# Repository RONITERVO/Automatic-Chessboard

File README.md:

# Automatic Chessboard

Arduino firmware for a CoreXY automatic chessboard with:

- two STEP/DIR stepper-motor drivers;
- an electromagnet for moving pieces;
- a multiplexed 8x8 reed-sensor matrix;
- a 16x2 I2C LCD and two-button interface; and
- the Micro-Max chess engine.

This is a substantially modified implementation of Greg06's
[Automated Chessboard](https://www.instructables.com/Automated-Chessboard/),
adapted around salvaged 3D-printer mechanics and the tested electronics
documented in this repository. See [design lineage and
attribution](ATTRIBUTION.md) and the repository's
[multi-license map](LICENSE.md) before redistributing it.

The [immersive 3D simulator](https://ronitervo.github.io/Automatic-Chessboard/) presents the complete assembly, chess pieces, setup process, physical controls, LCD, Arduino signal flow, wiring, and full-history replay in one shared React Three Fiber world. Visitors can use mouse, touch, or supported WebXR hands/controllers at real-world scale while the compiled production Nano HEX drives power-on, calibration, reed sensing, Micro-Max decisions, STEP/DIR motion, and magnet control. The standalone experience exposes Bluetooth as disconnected and never requests a real device. It is published automatically from `site/` after changes reach `main`.

## Demo

https://github.com/user-attachments/assets/5234de29-f910-4aed-a476-050bdca1a51d

## Hardware assumptions

The sketch uses the pin assignments and motion calibration in `global.h`. The
motor interface expects STEP/DIR drivers such as the A4988; motor current and
microstep selection are configured on the driver hardware.

For a complete beginner-oriented build, start with the
[`hardware` build guide](hardware/README.md). It includes protected power
wiring, a BOM, exact Nano/MKS Gen L V1.0 and 64-square sensor maps, staged assembly,
commissioning checks, diagrams, photographs of the working prototype, and
rework notes for the operational long PCB whose design predates the current
Bluetooth and A6 additions. Its archived KiCad source is reference-only, not a
current fabrication release. The 5 V buck output belongs on the Nano `5V` pin,
not `VIN`.

## Building

The release build is reproducible from PowerShell:

```powershell
./firmware/test.ps1 -InstallDependencies
```

It pins the AVR core and display libraries, validates the hardware contract,
runs tool tests, compiles the classic Nano and MKS Gen L V1.0 profiles, and
enforces flash/SRAM budgets. See [`firmware/README.md`](firmware/README.md) for the
modular source layout, explicit upload command, and contributor policy. The
main `.ino` can still be opened normally in Arduino IDE; its sibling `.ino`
tabs are compiled together automatically.

Review the pin assignments, travel calibration, limit-switch behavior, driver
current limit, and microstep settings before powering the motion hardware.

## Full validation without motion

When motors, piece magnets, or trustworthy reed readings are unavailable, run:

```powershell
./test-no-motion.ps1 -Port COM7
```

The workflow compiles the Nano firmware, enforces its memory budgets, exhaustively
tests the motionless `PLAN` / `DRAG` / `COMMIT` occupancy model, runs Windows and
Android planner/protocol/simulator tests, builds both apps, and optionally samples
the real Nano over USB. The COM probe is allowlisted to `HELLO 5.1.0`, `INFO`,
`TELEM`, and `BOARD`; it validates BOARD framing but does not require any particular
occupancy. It never uploads firmware or requests calibration, motor steps, magnet
power, or a chess move.

The probe first tries to keep DTR/RTS inactive. If a classic Nano does not
answer without its normal USB reset, use `-AllowSerialReset` only after checking
that firmware startup cannot energize the mechanism; this still does not send
an upload or any motion-capable protocol command.

This is the strongest release test possible without actuation, but it cannot prove
motor direction or step accuracy, magnet current/pickup/release, reed wiring and
orientation, mechanical clearance, homing repeatability, or physical collision
behavior. Those remain staged commissioning checks.

## Windows and Bluetooth companion

`windows_app` is the public-ready, open-source Windows monitor and companion for
this firmware. Windows runs Stockfish 18 and full chess rules while the Nano
retains motor timing, sensor scanning, calibration, limit checks, and Micro-Max
as a standalone fallback. It supports the Nano USB port, HC-08 BLE using the
default `FFE0`/`FFE1` service, and a no-hardware simulator for contributors.

Run `windows_app/setup.ps1` once, then `windows_app/run.ps1`. The visual Monitor
shows physical occupancy mismatches, carriage state, magnet command, limit
inputs, firmware memory, uptime, and connection freshness. Guided diagnostics,
structured logs, privacy-sanitized support bundles, optional local camera view,
automatic reconnect, and guarded developer controls are included. Start with
**Diagnostics -> Run safe diagnostics**; it never moves hardware. **Start game
and calibrate** intentionally begins physical movement.

The HC-08 receives commands on D10 through a receive-only software UART and
gets replies from hardware TX/D1. D0 remains dedicated to the onboard USB
bridge, so Bluetooth and USB transmitters never fight electrically. To free
D10, Button B/black limit uses analog-only A6 with a required external 10 kOhm
pull-up to 5 V. The HC-08 RX input must receive 3.3 V logic through a divider.
See `windows_app/README.md` for the complete wiring and first-start procedure.

Firmware 5.1.0 makes software occupancy authoritative. The reed matrix is read
only when a human requests move detection with Button A. The LCD proposes the
move; a second A press accepts it, while B opens square correction. Starting
pieces and robot moves are never checked against the reeds. A false reading
cannot stop a game. Both apps use the same workflow and exact `HELLO 5.1.0`
release handshake. See [Human-confirmed play](firmware/HUMAN_MOVE_INPUT.md) for
controls, correction, captures, and companion behavior.

Host-planned rearrangements still use straight orthogonal drags, explicit
capture removal, and independently tracked software occupancy. En passant,
promotion, and standard castling are included. Motor faults, calibration,
magnet timeout, `STOP`, and the single-byte `!` halt retain their behavior.

For local Micro-Max play, firmware 5.1.0 automatically carries knights and
blocked direct moves through the shortest available sequence of empty,
orthogonally adjacent square centres. It retains manual placement only when no
empty route connects the move endpoints. If a capture itself cannot reach the
bin, the player may remove it when prompted; after confirmation, the Nano
reruns the route search and completes the AI move automatically when possible.

Boards with missing, intermittent, or deliberately unused reed switches can use
the explicit **Move by tapping app** mode in either companion. Both human and
Stockfish moves then originate in the app and use the same physical route
planner. The app and Nano maintain matching virtual occupancy and ignore reed
readings for that entire game. The user visually confirms every completed move;
any mismatch or lost connection stops play and requires inspection and a new
calibrated session. This is an explicit authority choice, never an automatic
fallback from failed sensors.

Reproducible resource-budgeted builds, measured calibration references, the
configurable connected endurance tool, the 30-second continuous-magnet timeout,
normalized sensor coordinates, guarded calibration/direct movement, and the
best-effort `!` halt remain available. Bluetooth and cameras are not safety
systems, so a local physical power cutoff remains required for remote operation.

## Android Bluetooth companion

`android_app` provides the same working range from a phone: native HC-08 BLE
with reconnect, live logical/physical board comparison, Stockfish 18 play,
the same collision-safe blocker rearrangement and verified route transaction as
Windows, guided safe diagnostics, phone and network-camera views, PGN export,
structured logs, privacy-sanitized support ZIPs, a hardware-free simulator,
guarded raw commands, and a persistent best-effort halt control. Every page uses
a fixed, adaptive layout with pagination instead of horizontal or vertical
scrolling.

Run `android_app/download-stockfish.ps1`, then open `android_app` in Android
Studio or run `android_app/gradlew.bat assembleDebug`. See
[`android_app/README.md`](android_app/README.md) for installation, safety, and
contributor guidance.

## Motor-driver configuration

`MOTOR_MICROSTEPS` in `global.h` must match the hardware configuration of both
motor drivers. For an A4988, the common modes are:

| Microsteps | MS1 | MS2 | MS3 |
| ---: | :---: | :---: | :---: |
| 1 | LOW | LOW | LOW |
| 2 | HIGH | LOW | LOW |
| 4 | LOW | HIGH | LOW |
| 8 | HIGH | HIGH | LOW |
| 16 | HIGH | HIGH | HIGH |

The current high-friction-drive profile remains in full-step mode
(`MOTOR_MICROSTEPS = 1`). Its measured working value uses a fixed fast step
interval; avoiding slow ramps prevents the prototype's strong low-speed
resonance. If the driver jumpers or wiring are changed later, change this
constant to the same value. The firmware then scales the steps per square,
homing limit, and step intervals to preserve the existing travel distance and
approximate physical speeds.

Set the driver current limit from the motor's rated phase current and the sense
resistors fitted to the particular driver board. For an A4988, consult that
board's documentation before using the common `Imax = Vref / (8 * Rsense)`
calculation; clone boards use different sense-resistor values. Never move a
driver or motor connection while motor power is applied.

## Calibration approach safety

Calibration always seeks the white switch before the black corner switch. If a
known trolley position is above rank 6, the unloaded head first moves down to
rank 6. If the black switch is already active, the head moves one full square
away to clear that lane. The staging move never travels toward the black switch.

During normal calibration both switches are approached one step at a time. The
white switch stays pressed while the black switch is found. Capture recovery and
developer reference calibrations use the same sequence. After both switches
establish the corner, the head moves directly to the exact e6 park offset with
no separate release/backoff stage or switch-specific release-distance setting.

The shared button inputs act only as endstops during calibration, so they cannot
abort calibration. Use the board's power switch for an emergency stop during
this sequence. Button emergency stops remain enabled for normal board and test
movements outside calibration.

Every successful calibration and endurance-test reference pass parks the head at
e6. This keeps the normal power-cycle and new-game starting position out of the
black-switch lane before the next white-switch approach.

## Power-cycle position memory

The firmware journals head positions across 32 EEPROM slots. Before the first
step of any motor movement it commits an `UNKNOWN` record. A new board-square
coordinate is committed only after the head reaches that stable endpoint. The
journal spreads writes across slots and commits each record last, so an
interrupted EEPROM write leaves the preceding complete record available.

Immediately after power-up the LCD displays `LAST HEAD` and either the saved
square or `??`. A saved coordinate is used only to stage calibration safely; it
does not bypass calibration or enable normal movement. For example, a head
saved at e8 first moves away from the corner to rank 6 before seeking the white
calibration switch.

Switching power off while the head is stopped preserves its displayed square.
Switching power off during movement produces `POS UNKNOWN` on the next boot,
because no coordinate can safely represent a partially completed move. The
saved square also assumes the unpowered head has not been moved by hand or
shifted mechanically after the motors lose holding torque.

Calibration is blocked when the position is unknown and the black switch is
not already active. The LCD asks for the unpowered head to be placed at rank 6
or below; after the next startup, select calibration and confirm `A=READY`.
This recovery confirmation is also required on the first boot after installing
firmware that has no valid position journal yet.

## Connected endurance test

Firmware 4.0 and later move the former fixed on-device AI self-play workload to the
configurable [`firmware/endurance_test.py`](firmware/endurance_test.py) tool.
Firmware 4.4 uses that guarded, developer-only `PATH` command only for
horizontal, vertical, and 45-degree square-centre paths; continuous knight or
S-shaped travel is deliberately rejected.
The magnet is forced off, results are logged on the computer, cycle count and
reference frequency are configurable, and both homing step counts are compared
against a measured baseline. See [`firmware/README.md`](firmware/README.md) for
the exact command and physical safety requirements.

This test detects accumulated position drift using the existing switches. It
cannot prove that no individual missed step was later cancelled in the opposite
direction; detecting every stall in real time requires motor encoders or a
driver with suitable diagnostic feedback.

## Builder geometry measurement

Firmware 4.5 keeps board geometry as four compile-time constants, with no
geometry EEPROM or runtime configuration. The Windows and Android companions
provide the measurement interface so the Nano's local controls stay focused on
play and calibration. After normal calibration, open **Board alignment** on
Windows or **Move > Align board** on Android, select a square, and start the
recommended head-only session. Use the four one-step controls until the head is
visually centered, then record the point. A magnetic marker is optional and
requires the separate safety confirmation.

Measure two widely separated squares with different files and ranks. The apps
show the exact four source values to edit in [`global.h`](global.h), including
correct handling of non-default microstepping. The session never writes EEPROM
or changes installed geometry, and it reverses all nudges when finished. It
marks the head position unknown before the first nudge, so calibration is
mandatory even after disconnect or power loss.

For terminal-only work, send `GEOMETRY`, then `ALIGN <square> H`, use `NUDGE
X+|X-|Y+|Y-`, record the `ALIGN ACTIVE` offsets, and finish with `ALIGN END`.
The optional offline calculator accepts the two recorded reports:

```powershell
python ./firmware/geometry_calculator.py `
  "GEOMETRY a2 X+3 Y-1" "GEOMETRY h7 X+10 Y-6"
```

Edit the four reported constants, upload, calibrate again, and verify at least
four widely separated squares. This corrects translation and independent axis
scale; a rotated, skewed, or nonuniform board must be aligned mechanically.
The removed local maintenance carousel and duplicate sensor screen reduce Nano
flash and SRAM; both apps and the `BOARD` command retain complete diagnostics.

## Piece-retention travel planner

The standalone planner accepts direct carried moves only when
their square centres share a file, rank, or diagonal. It does not attempt a
continuous knight or S-shaped carry. Connected play represents those moves as
separate verified square-centre drags. Capture removal and the rook part of
castling retain explicit horizontal/vertical segments to reach their
necessary off-board or temporarily obstructed destinations.
Standalone carries also preflight every traversed square; diagonal steps
require both shared orthogonal corner squares to be empty. An unsafe direct
carry becomes a manual, human-confirmed move before the magnet is energized.

Knights and blocked direct moves use shortest empty orthogonal routes. When
no route exists, the LCD requests manual placement. Complete the displayed move
and press A; the Nano trusts that confirmation and continues without scanning.

Captures first search all a-file bin exits. If the captured piece is trapped,
remove the displayed piece and press A. The Nano retries the remaining carry
using software occupancy and requests a second manual placement only if needed.

For connected play, `windows_app/routing.py` searches labeled board
configurations. It uses only orthogonal square-to-square carried paths, so the
physical diagonal-clearance constraint is satisfied conservatively. Turning
paths are split at square centres into straight `DRAG` commands verified against software occupancy.
The search minimizes disturbed pieces first, then actual magnet pickups,
distance, and turns. Hardware-validated side-adjacent pieces do not penalize an
otherwise empty orthogonal route. Time, node, parking, corridor,
temporary-piece, and recursion limits prevent unbounded optimization work.
Before search,
the planner classifies the exact 8×8 labeled-pebble reachability cases; ordinary
chess positions have enough empty squares to be structurally reachable. If
bounded optimization cannot finish, a reversible dense-board constructor can
return a replay-validated safe plan. It is marked non-optimal. Failure still
stops the move when neither method produces a validated plan.

Every corridor ends on an exact whole-step destination, with no interpolation
rounding to accumulate between moves. Firmware 4.4 also removes unequal-ratio
CoreXY interpolation below every caller: each displacement is one or more pure
horizontal, vertical, or 45-degree segments. Hardware validation uses a `1000`
microsecond half-period for start, carrying, and unloaded motion. Keeping these
equal intentionally avoids the mechanism's strong low-speed resonance.

## Captured-piece bin

Captured pieces are released into the bin along the calibration side. Supported
5.0 builds require unobstructed bin and carriage clearance beside the complete
`a1`-`a8` edge; this is the geometry used by the repository designs.
The calibrated e6 park position places the left limit at approximately `x = 0.35` in
board-square coordinates; the playing-field edge is `x = 0.50`. Release uses a
conservative `x = 0.48` center line, just outside the playing field and about
25 full steps away from the limit switch.

For every capture, the piece reaches an `a`-file square centre and then follows
that rank directly to the left-side release point. The final axial segment uses
the normal carrying speed and finishes before magnet release.
The head remains stationary through the magnet's release delay and for another
400 ms while the piece falls into the bin. It then immediately
homes both axes from the nearby calibration side and restores the known e6
position before moving the AI piece. Nothing is stored on the travel rail, so
later captures cannot collide with earlier ones.

Capture behavior remains covered by normal standalone and connected game paths.
The magnet-free endurance test intentionally focuses on repeatable production
board travel; capture-bin testing requires a guarded physical-piece test.

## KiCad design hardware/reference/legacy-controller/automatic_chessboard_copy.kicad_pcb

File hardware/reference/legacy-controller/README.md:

# Working prototype PCB and legacy design reference

The existing fabricated long PCB is functional and runs the photographed
prototype after external wire and resistor modifications. **Do not manufacture
the archived PCB design unchanged and do not generate production Gerbers from
it.**

These KiCad files are preserved because their long component layout matches
the physical working board and can help explain how the modules were arranged.
They predate current firmware 4.6.0 wiring and are not the electrical source of
truth or a verified fabrication release.

## Required rework for the current prototype

When reusing an already fabricated board, implement the complete
`../../connections.csv` contract. In particular:

- leave the legacy D10 switch connector unused;
- connect HC-08 `TXD` through 1 kohm to Nano `D10`;
- wire the second normally-open switch between Nano `A6` and GND;
- add a 10 kohm pull-up from `A6` to 5 V;
- connect Nano `D1/TX` through 1 kohm to HC-08 `RXD`, and add 2 kohm from that
  divider node to GND; and
- complete the sensor, motor, power, and load connections that are not routed
  by the board using insulated, strain-relieved external wiring.

Do not plug the second switch into the old D10 position: D10 is now the
firmware's receive input for Bluetooth. Verify every modification by net name
and meter continuity rather than copying wire colors from a photograph. The
[working-prototype page](../../PROTOTYPE.md) shows the physical board and its
external rework.

Known limitations include:

- sensor-channel and several motor/load connections were completed with
  external wiring rather than PCB traces;
- the historical schematic contains 89 explicit no-connect markers, including
  the multiplexer channel area;
- the driver `RESET`/`SLEEP` pair is not explicitly routed to 5 V;
- it predates the HC-08 on D10, the A6 switch/pull-up change, and the current
  5 V power recommendation;
- the historical power labels include a 12 V/VIN arrangement that is not used
  by the current 24 V plus regulated-5 V design;
- no current-limit, fuse, emergency cutoff, reverse-polarity, enclosure, or
  production verification is encoded in the PCB source;
- no DRC/ERC or manufacturing review has been certified for these files.

Use `../../WIRING.md`, `../../connections.csv`, and `../../sensor-map.csv` for
the current build. The archive intentionally contains no Gerbers, drill files,
pick-and-place files, or fabrication ZIP. An existing board being operational
does not remove the need for the current public-build fuses, cutoff, polarity
protection, verified 5 V supply, and commissioning checks.

Files:

- `automatic_chessboard_copy.kicad_pcb`: long board layout matching the
  photographed controller form.
- `automatic_chessboard_copy.kicad_pro`: historical KiCad project settings.
- `reference-schematic.kicad_sch`: related historical circuit drawing; layout
  and present-day wiring do not fully match it.

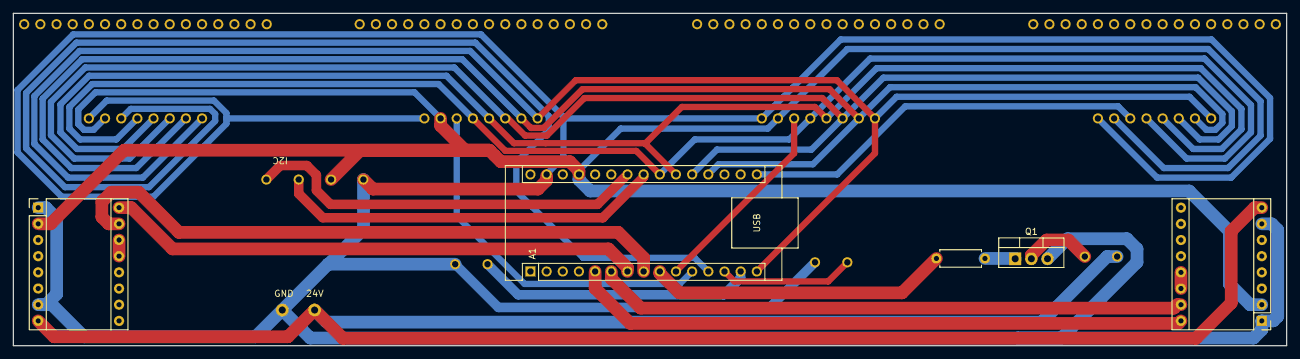
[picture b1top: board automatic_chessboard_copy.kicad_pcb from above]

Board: 2 copper layers, 200.0 x 52.2 mm, 14 parts (0 on the bottom side), 25 nets.

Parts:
A1: Arduino Nano; Arduino_Nano
A2, A3: A4988; Pololu_Breakout-16_15.2x20.3mm
I2C: i2c display
L1: L; electromagnet_pins
Q1: TIP120; TO-220-3_Vertical
R1: 1k; R_Axial_DIN0207_L6.3mm_D2.5mm_P7.62mm_Horizontal
SW1, SW2: SW_Push; button_pins
U1, U2, U3, U4: CD74HC4067M; multiplexer
U6: Power

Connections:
+24V: A2.8 (VMOT), A3.8 (VMOT), L1.1, U6.2 (24V)
/5v: A1.27 (+5V), A2.2 (VDD), A3.2 (VDD), I2C.2 (VCC), U1.24 (VCC), U2.24 (VCC), U3.24 (VCC), U4.24 (VCC)
/A0: A1.19 (A0), U1.13 (S3), U2.13 (S3), U3.13 (S3), U4.13 (S3)
/A1: A1.20 (A1), U1.14 (S2), U2.14 (S2), U3.14 (S2), U4.14 (S2)
/A2: A1.21 (A2), U1.11 (S1), U2.11 (S1), U3.11 (S1), U4.11 (S1)
/A3: A1.22 (A3), U1.10 (S0), U2.10 (S0), U3.10 (S0), U4.10 (S0)
/D2: A1.5 (D2), A3.16 (DIR)
/D3: A1.6 (D3), A3.15 (STEP)
/D4: A1.7 (D4), A2.16 (DIR)
/D5: A1.8 (D5), A2.15 (STEP)
/D6: A1.9 (D6), R1.1
/D7: A1.10 (D7), U2.15 (~E)
/D8: A1.11 (D8), U3.15 (~E)
/D9: A1.12 (D9), U4.15 (~E)
/D10: A1.13 (D10), SW1.2
/D11: A1.14 (D11), SW2.2
/D12: A1.15 (D12), U1.1 (COM), U2.1 (COM), U3.1 (COM), U4.1 (COM)
/D13: A1.16 (D13), U1.15 (~E)
/SCL: A1.24 (A5), I2C.4 (SCL)
/SDA: A1.23 (A4), I2C.3 (SDA)
GND: A1.29 (GND), A2.1 (GND), A2.7 (GND), A3.1 (GND), A3.7 (GND), I2C.1 (GND), Q1.3 (E), SW1.1, SW2.1, U1.12 (GND), U2.12 (GND), U3.12 (GND), U4.12 (GND), U6.1 (GND)
unnamed: A2.13 (~RESET), A2.14 (~SLEEP)
unnamed: A3.13 (~RESET), A3.14 (~SLEEP)
unnamed: Q1.1 (B), R1.2
unnamed: L1.2, Q1.2 (C)

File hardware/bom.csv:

category,quantity,item,minimum_specification,tested_reference,status
controller,1,Arduino Nano,Classic ATmega328P 5V 16MHz,Nano-compatible USB-C clone,required
sensors,4,16-channel multiplexer breakout,CD74HC4067-compatible 5V active-low enable,WAVGAT CD74HC4067 breakout,required
sensors,64,Normally-open glass reed switch,Closes reliably through selected tile and piece gap,Glass reed in printed tile slot,required
motion,2,Stepper driver carrier,A4988 or HR4988 StepStick pinout 24V capable with heatsink,HR4988SQ with two R100 resistors,required
motion,2,Bipolar stepper motor,4-wire NEMA17 1.8deg preferred >=0.20Nm and current matched to driver,Unlabelled JGAurora A3S donor motor,required
motion,2,VMOT capacitor,100uF >=50V electrolytic 105C preferred,100uF 50V,required
magnet,1,Electromagnet,24V DC approximately 2.8W,H2520 24V 2.8W,required
magnet,1,NPN Darlington,TIP120 or validated logic-level MOSFET alternative,TIP120,required
magnet,1,Flyback diode,1A >=50V axial diode,1N4004-1N4007 equivalent,required
magnet,1,Base resistor,1kohm 0.25W,1kohm,required
magnet,1,Base pull-down resistor,10kohm 0.25W,None on prototype,safety addition
interface,1,16x2 I2C LCD,5V PCF8574 backpack address 0x27,Blue 16x2 module,required
interface,2,Normally-open momentary microswitch,Actuated before mechanical hard stop,Shared button and limit switch,required
interface,1,A6 pull-up resistor,10kohm 0.25W,Inside heat-shrink,required
bluetooth,1,HC-08 BLE UART carrier,Carrier accepts 5V supply and uses 3.3V UART logic,HC-08 carrier,required for BLE
bluetooth,2,1kohm resistor,0.25W,Inside heat-shrink,required for BLE
bluetooth,1,2kohm resistor,0.25W,Inside heat-shrink,required for BLE
power,1,24V DC supply,Enclosed regulated isolated 3A minimum 5A recommended,Unbranded 24V 10A brick,required
power,1,Buck converter,24V input 5.0V output >=1A continuous and >=36V input recommended,Unlabelled adjustable buck,required
protection,1,Main fuse and holder,3A time-delay starting value >=32VDC; 5A maximum only after load measurement,None on prototype,safety addition
protection,1,Latching cutoff,>=30VDC 5A and reachable,None on prototype,safety addition
protection,1,Reverse-polarity protection,>=30VDC 5A,None on prototype,safety addition
protection,1,Logic fuse,1A >=32VDC,None on prototype,safety addition
wiring,as needed,Main power wire,0.75mm2 or 18AWG copper recommended,Mixed prototype wire,required
wiring,as needed,Branch and motor wire,0.34mm2 or 22AWG copper recommended,Mixed prototype wire,required
wiring,as needed,Logic and sensor wire,0.14-0.25mm2 or 26-24AWG strain-relieved,Ribbon and hookup wire,required
